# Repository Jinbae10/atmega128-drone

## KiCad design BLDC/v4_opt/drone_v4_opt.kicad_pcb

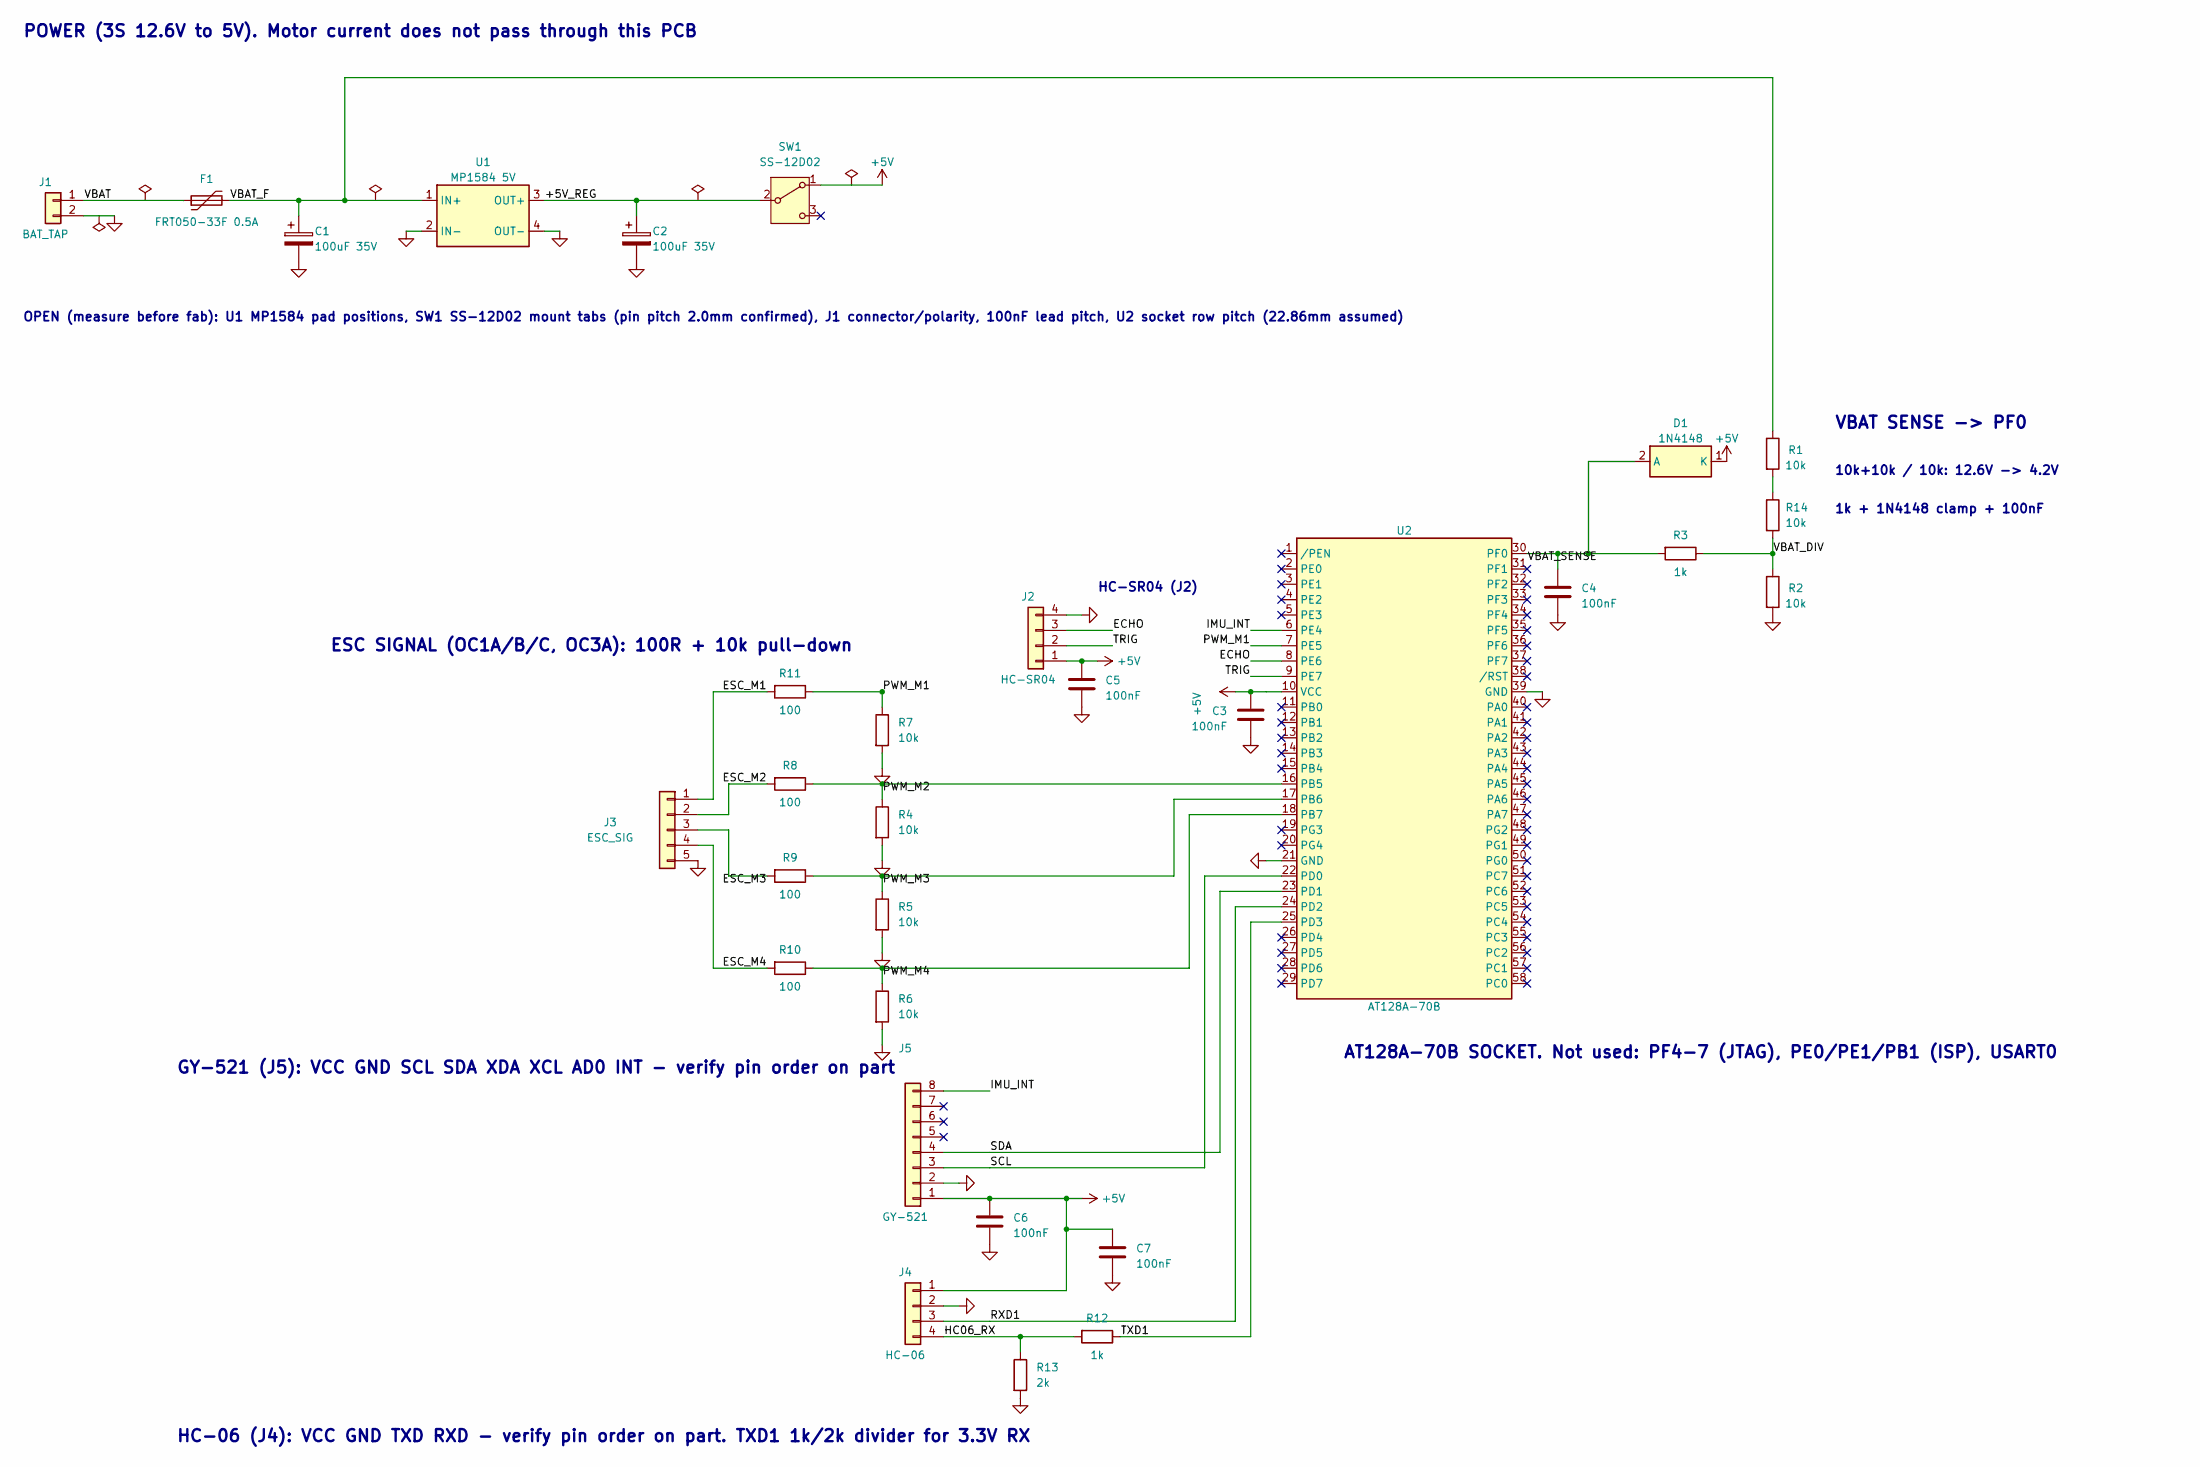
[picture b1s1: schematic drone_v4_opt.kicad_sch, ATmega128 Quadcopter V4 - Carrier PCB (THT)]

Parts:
C1, C2: 100uF 35V; CP_Radial_D6.3mm_P2.50mm
C3, C4, C5, C6, C7: 100nF; C_Disc_D4.3mm_W1.9mm_P5.00mm
D1: 1N4148; D_DO-35_SOD27_P7.62mm_Horizontal
F1: FRT050-33F 0.5A; Fuse_FRT050-33F_P5.10; MPN FRT050-33F
J1: BAT_TAP; PinHeader_1x02_P2.54mm_Vertical
J2: HC-SR04; PinSocket_1x04_P2.54mm_Vertical
J3: ESC_SIG; PinHeader_1x05_P2.54mm_Vertical
J4: HC-06; PinSocket_1x04_P2.54mm_Vertical
J5: GY-521; PinSocket_1x08_P2.54mm_Vertical
R1, R2, R4, R5, R6, R7, R14: 10k; R_Axial_DIN0204_L3.6mm_D1.6mm_P7.62mm_Horizontal
R3, R12: 1k; R_Axial_DIN0204_L3.6mm_D1.6mm_P7.62mm_Horizontal
R8, R9, R10, R11: 100; R_Axial_DIN0204_L3.6mm_D1.6mm_P7.62mm_Horizontal
R13: 2k; R_Axial_DIN0204_L3.6mm_D1.6mm_P7.62mm_Horizontal
SW1: SS-12D02; SW_SS-12D02_P2.00
U1: MP1584 5V; MP1584_Module_22x17
U2: AT128A-70B; AT128A-70B_Socket

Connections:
+5V: C3.1, C5.1, C6.1, C7.1, D1.1 (K), J2.1, J4.1, J5.1, SW1.1 (A), U2.10 (VCC)
/+5V_REG: C2.1, SW1.2 (B), U1.3 (OUT+)
/ECHO: J2.3, U2.8 (PE6)
/ESC_M1: J3.1, R11.2
/ESC_M2: J3.2, R8.2
/ESC_M3: J3.3, R9.2
/ESC_M4: J3.4, R10.2
/HC06_RX: J4.4, R12.2, R13.1
/IMU_INT: J5.8, U2.6 (PE4)
/PWM_M1: R7.1, R11.1, U2.7 (PE5)
/PWM_M2: R4.1, R8.1, U2.16 (PB5)
/PWM_M3: R5.1, R9.1, U2.17 (PB6)
/PWM_M4: R6.1, R10.1, U2.18 (PB7)
/RXD1: J4.3, U2.24 (PD2)
/SCL: J5.3, U2.22 (PD0)
/SDA: J5.4, U2.23 (PD1)
/TRIG: J2.2, U2.9 (PE7)
/TXD1: R12.1, U2.25 (PD3)
/VBAT: F1.1, J1.1
/VBAT_DIV: R2.1, R3.1, R14.2
/VBAT_F: C1.1, F1.2, R1.1, U1.1 (IN+)
/VBAT_SENSE: C4.1, D1.2 (A), R3.2, U2.30 (PF0)
GND: C1.2, C2.2, C3.2, C4.2, C5.2, C6.2, C7.2, J1.2, J2.4, J3.5, J4.2, J5.2, R2.2, R4.2, R5.2, R6.2, R7.2, R13.2, U1.2 (IN-), U1.4 (OUT-), U2.21 (GND), U2.39 (GND)
unnamed: R1.2, R14.1

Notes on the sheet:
POWER (3S 12.6V to 5V). Motor current does not pass through this PCB
OPEN (measure before fab): U1 MP1584 pad positions, SW1 SS-12D02 mount tabs (pin pitch 2.0mm confirmed), J1 connector/polarity, 100nF lead pitch, U2 socket row pitch (22.86mm assumed)
VBAT SENSE -> PF0
10k+10k / 10k: 12.6V -> 4.2V
1k + 1N4148 clamp + 100nF
AT128A-70B SOCKET. Not used: PF4-7 (JTAG), PE0/PE1/PB1 (ISP), USART0
HC-SR04 (J2)
ESC SIGNAL (OC1A/B/C, OC3A): 100R + 10k pull-down
GY-521 (J5): VCC GND SCL SDA XDA XCL AD0 INT - verify pin order on part
HC-06 (J4): VCC GND TXD RXD - verify pin order on part. TXD1 1k/2k divider for 3.3V RX

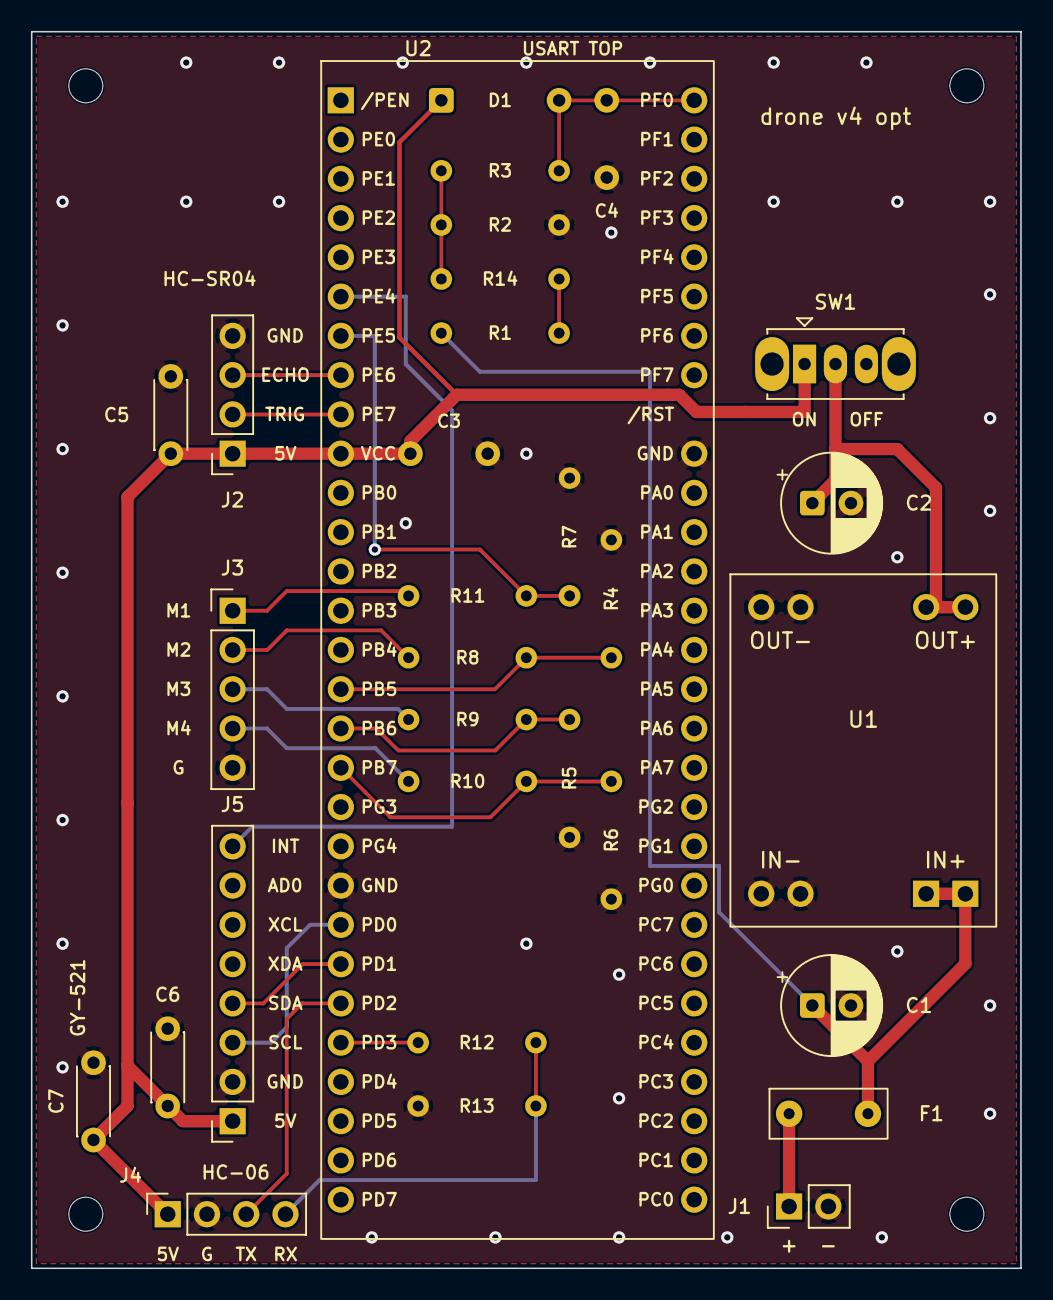
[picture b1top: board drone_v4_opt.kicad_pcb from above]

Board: 2 copper layers, 64.0 x 80.0 mm, 35 parts (0 on the bottom side), 24 nets.

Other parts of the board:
MH1, MH2, MH3, MH4: MountingHole_2.2mm

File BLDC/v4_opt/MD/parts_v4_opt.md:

# 부품 목록 (v4_opt, 최종)

- 기준일: 2026-11-18. 값·수량은 [drone_v4_opt.kicad_sch](../drone_v4_opt.kicad_sch) BOM 기준(v4와 소자·수량 동일, 배치·MCU 핀만 다름).
- 가격은 **VAT 포함**, 디바이스마트 상품 페이지 값(2026-11-17~18 확인). 상세 근거는 [../../v4/MD/parts_v4.md](../../v4/MD/parts_v4.md).
- **v4_opt 주의**: 모듈(U2) 아래에 저항 14개·D1·C3·C4가 들어가므로 U2 암헤더는 반드시 **8.5mm 높이(VLT-PH054 Type 1)**. 저항·D1·C3·C4를 먼저 납땜한 뒤 암헤더를 납땜합니다.

## 1. 납땜 소자 (디바이스마트)

| 회로도 번호 | 소자 | 상품 | 필요 | 구매 단위 | 가격 |
|---|---|---|---|---|---|
| R1, R2, R4~R7, R14 | 10k 1/8W 1% (20k = R1+R14 직렬) | [no=1907](https://www.devicemart.co.kr/goods/view?no=1907) | 7 | 10개 | 330원 |
| R3, R12 | 1k 1/8W | [no=2150](https://www.devicemart.co.kr/goods/view?no=2150) | 2 | 10개 | 165원 |
| R13 | 2k 1/8W | [no=2146](https://www.devicemart.co.kr/goods/view?no=2146) | 1 | 10개 | 165원 |
| R8~R11 | 100Ω 1/8W | [no=2166](https://www.devicemart.co.kr/goods/view?no=2166) | 4 | 10개 | 165원 |
| C3~C7 | 100nF 50V 적층 세라믹 | [no=1399](https://www.devicemart.co.kr/goods/view?no=1399) | 5 | 10개 | 330원 |
| F1 | 폴리퓨즈 FRT050-33F 0.5A 33V | [no=10918593](https://www.devicemart.co.kr/goods/view?no=10918593) | 1 | 10개 | 1,540원 |
| D1 | 1N4148 DO-35 | [no=25](https://www.devicemart.co.kr/goods/view?no=25) | 1 | 10개 | 220원 |
| C1, C2 | 전해 100µF 35V Ø6.3×11 | [no=12211007](https://www.devicemart.co.kr/goods/view?no=12211007) | 2 | 10개 | 440원 |
| SW1 | 슬라이드 SS-12D02 | [no=14572](https://www.devicemart.co.kr/goods/view?no=14572) | 1 | 1개 | 165원 |
| J1, J3, U1 장착 | 수 핀헤더 1×40 2.54mm | [no=2825](https://www.devicemart.co.kr/goods/view?no=2825) | 1줄 | 1줄 | 220원 |
| | | | | **소계** | **약 3,740원** |

## 2. 모듈 (디바이스마트)

| 부품 | 상품 | 수량 | 가격 |
|---|---|---|---|
| MPU-6050 GY-521 | [no=1247052](https://www.devicemart.co.kr/goods/view?no=1247052) | 1 | 4,950원 |
| HC-06 DIP 슬레이브 | [no=1376882](https://www.devicemart.co.kr/goods/view?no=1376882) | 1 | 6,050원 |
| MP1584 강압 모듈 SZH-PWSD-002 | [no=1321132](https://www.devicemart.co.kr/goods/view?no=1321132) | 1 | 2,200원 |
| | | **소계** | **13,200원** |

## 3. PCB 밖 (디바이스마트)

| 부품 | 상품 | 수량 | 가격 |
|---|---|---|---|
| 암 핀헤더 1×40 **8.5mm** (VLT-PH054) — U2·센서 소켓 | [no=15959307](https://www.devicemart.co.kr/goods/view?no=15959307) | 3 (2개면 74핀 충분, 1개 예비) | 1,320원 |
| XT60 암수 세트 | [no=1078005](https://www.devicemart.co.kr/goods/view?no=1078005) | 2 | 3,520원 |
| 열수축 튜브 5파이 1m | [no=1065347](https://www.devicemart.co.kr/goods/view?no=1065347) | 1 | 253원 |
| 프로펠러 SMG 5030 2엽 CW/CCW | [no=1342513](https://www.devicemart.co.kr/goods/view?no=1342513) | 3쌍 | 8,580원 |

## 4. 합계 (VAT 포함)

| 구분 | 금액 |
|---|---|
| 납땜 소자 | 약 3,740원 |
| 모듈 | 13,200원 |
| PCB 밖 (암헤더·XT60·열수축·프로펠러) | 13,673원 |
| **디바이스마트 부품 합계** | **약 30,613원** |
| PCB 제작 (사용자 확인 가격, 64×80mm 조건 미확인) | 19,000원 |
| 배송비 | 2,700원 |
| **디바이스마트 총액** | **약 52,313원** |

- 2026-11-18 장바구니(PCB 제외): 33,313원(배송 포함).
- `parts_v4.md` 합계(29,293원)에는 암헤더 1,320원이 빠져 있어 여기서는 포함했습니다.
- 이미 구매: 모터 MT2204 2300KV ×4, ESC LittleBee-Spring 20A ×4, 3S LiPo 1300mAh 90C XT60, 충전기 Imax B3 Pro. 보유·대여: HC-SR04, ATmega128A 모듈, JTAG ICE, AR-UART2USB.

## 5. 주문 전 확인

1. 100nF 리드 간격, SS-12D02 고정 탭, MP1584 모듈 패드 위치 (실측)
2. SW1 ON 방향(실크 ON/OFF는 추정) — 멀티미터 확인
3. 암헤더 높이 8.5mm 제품인지 확인

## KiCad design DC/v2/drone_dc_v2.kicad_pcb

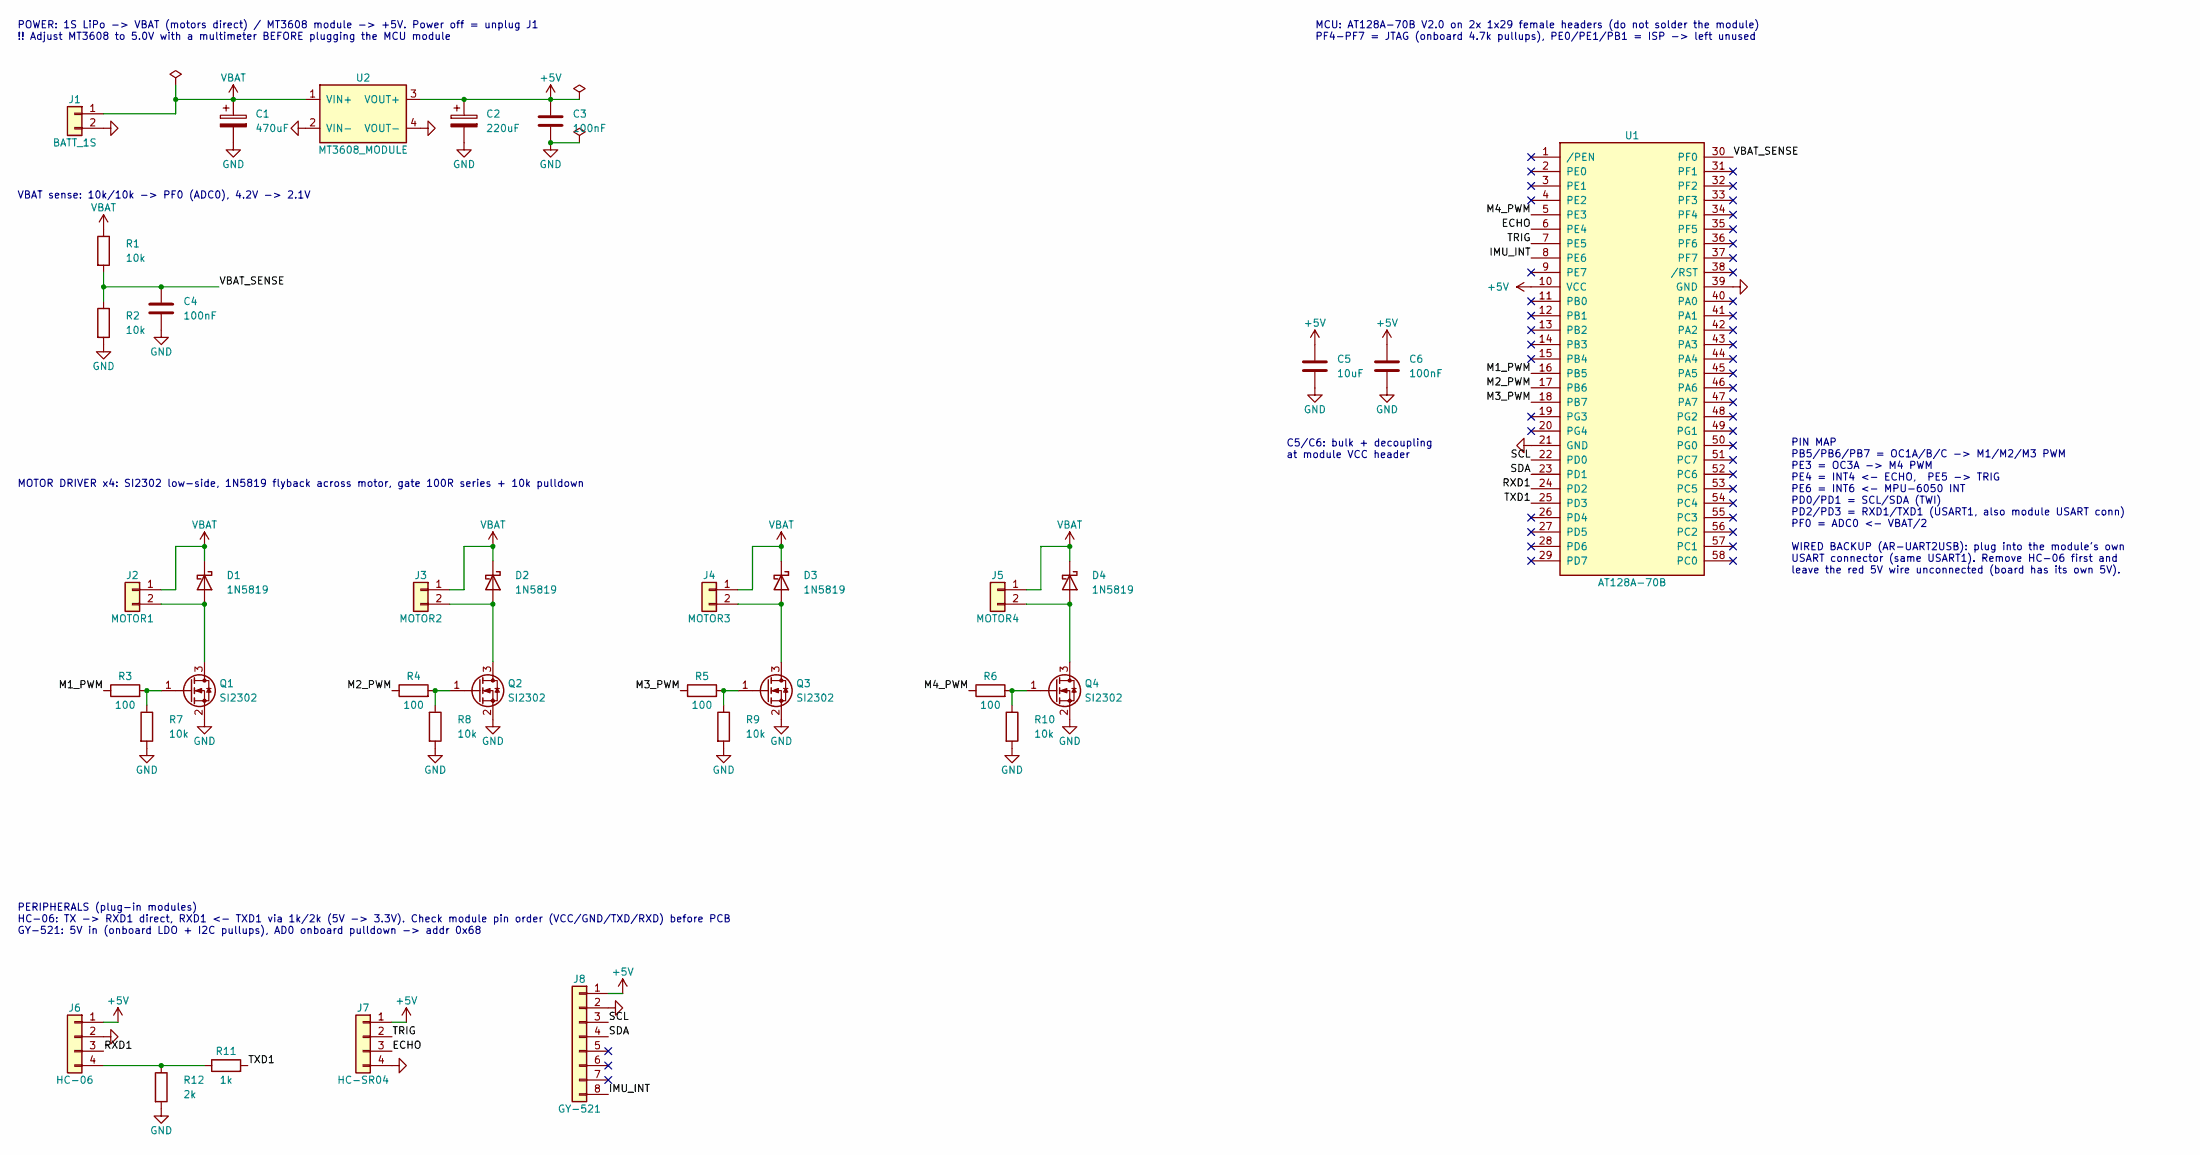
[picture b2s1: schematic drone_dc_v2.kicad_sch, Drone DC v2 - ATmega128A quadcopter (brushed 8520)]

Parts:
C1: 470uF; CP_Radial_D8.0mm_P3.50mm
C2: 220uF; CP_Radial_D6.3mm_P2.50mm
C3, C4, C6: 100nF; C_Disc_D3.0mm_W1.6mm_P2.50mm
C5: 10uF; CP_Radial_D5.0mm_P2.00mm
D1, D2, D3, D4: 1N5819; D_DO-41_SOD81_P5.08mm_Vertical_AnodeUp
J1: BATT_1S; JST_PH_B2B-PH-K_1x02_P2.00mm_Vertical
J2: MOTOR1; PinHeader_1x02_P2.54mm_Vertical
J3: MOTOR2; PinHeader_1x02_P2.54mm_Vertical
J4: MOTOR3; PinHeader_1x02_P2.54mm_Vertical
J5: MOTOR4; PinHeader_1x02_P2.54mm_Vertical
J6: HC-06; PinSocket_1x04_P2.54mm_Vertical
J7: HC-SR04; PinSocket_1x04_P2.54mm_Vertical
J8: GY-521; PinSocket_1x08_P2.54mm_Vertical
Q1, Q2, Q3, Q4: SI2302; SOT-23_Handsoldering
R1, R2, R7, R8, R9, R10: 10k; R_Axial_DIN0207_L6.3mm_D2.5mm_P2.54mm_Vertical
R3, R4, R5, R6: 100; R_Axial_DIN0207_L6.3mm_D2.5mm_P2.54mm_Vertical
R11: 1k; R_Axial_DIN0207_L6.3mm_D2.5mm_P2.54mm_Vertical
R12: 2k; R_Axial_DIN0207_L6.3mm_D2.5mm_P2.54mm_Vertical
U1: AT128A-70B; AT128A-70B_Module
U2: MT3608_MODULE; MT3608_Module_Wire

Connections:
+5V: C2.1, C3.1, C5.1, C6.1, J6.1, J7.1, J8.1, U1.10 (VCC), U2.3 (VOUT+)
/ECHO: J7.3, U1.6 (PE4)
/IMU_INT: J8.8, U1.8 (PE6)
/M1_PWM: R3.1, U1.16 (PB5)
/M2_PWM: R4.1, U1.17 (PB6)
/M3_PWM: R5.1, U1.18 (PB7)
/M4_PWM: R6.1, U1.5 (PE3)
/RXD1: J6.3, U1.24 (PD2)
/SCL: J8.3, U1.22 (PD0)
/SDA: J8.4, U1.23 (PD1)
/TRIG: J7.2, U1.7 (PE5)
/TXD1: R11.2, U1.25 (PD3)
/VBAT_SENSE: C4.1, R1.2, R2.1, U1.30 (PF0)
GND: C1.2, C2.2, C3.2, C4.2, C5.2, C6.2, J1.2, J6.2, J7.4, J8.2, Q1.2 (S), Q2.2 (S), Q3.2 (S), Q4.2 (S), R2.2, R7.2, R8.2, R9.2, R10.2, R12.2, U1.21 (GND), U1.39 (GND), U2.2 (VIN-), U2.4 (VOUT-)
unnamed: D1.2 (A), J2.2, Q1.3 (D)
unnamed: D2.2 (A), J3.2, Q2.3 (D)
unnamed: D3.2 (A), J4.2, Q3.3 (D)
unnamed: D4.2 (A), J5.2, Q4.3 (D)
unnamed: J6.4, R11.1, R12.1
unnamed: Q1.1 (G), R3.2, R7.1
unnamed: Q2.1 (G), R4.2, R8.1
unnamed: Q3.1 (G), R5.2, R9.1
unnamed: Q4.1 (G), R6.2, R10.1
VBAT: C1.1, D1.1 (K), D2.1 (K), D3.1 (K), D4.1 (K), J1.1, J2.1, J3.1, J4.1, J5.1, R1.1, U2.1 (VIN+)

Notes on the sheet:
POWER: 1S LiPo -> VBAT (motors direct) / MT3608 module -> +5V. Power off = unplug J1 !! Adjust MT3608 to 5.0V with a multimeter BEFORE plugging the MCU module
VBAT sense: 10k/10k -> PF0 (ADC0), 4.2V -> 2.1V
MOTOR DRIVER x4: SI2302 low-side, 1N5819 flyback across motor, gate 100R series + 10k pulldown
PERIPHERALS (plug-in modules) HC-06: TX -> RXD1 direct, RXD1 <- TXD1 via 1k/2k (5V -> 3.3V). Check module pin order (VCC/GND/TXD/RXD) before PCB GY-521: 5V in (onboard LDO + I2C pullups), AD0 onboard pulldown -> addr 0x68
MCU: AT128A-70B V2.0 on 2x 1x29 female headers (do not solder the module) PF4-PF7 = JTAG (onboard 4.7k pullups), PE0/PE1/PB1 = ISP -> left unused
C5/C6: bulk + decoupling at module VCC header
PIN MAP PB5/PB6/PB7 = OC1A/B/C -> M1/M2/M3 PWM PE3 = OC3A -> M4 PWM PE4 = INT4 <- ECHO, PE5 -> TRIG PE6 = INT6 <- MPU-6050 INT PD0/PD1 = SCL/SDA (TWI) PD2/PD3 = RXD1/TXD1 (USART1, also module USART conn) PF0 = ADC0 <- VBAT/2 WIRED BACKUP (AR-UART2USB): plug into the module's own USART connector (sa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

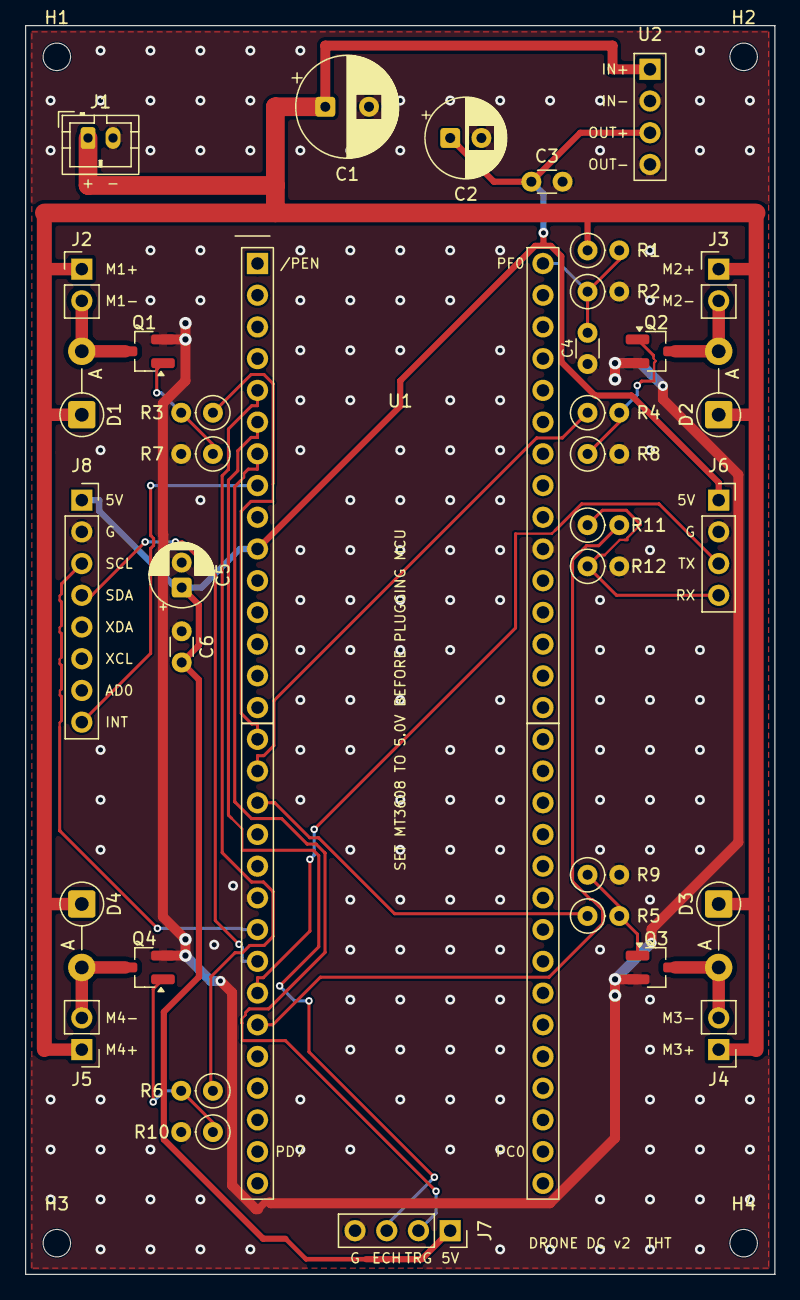
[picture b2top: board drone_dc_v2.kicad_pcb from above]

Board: 2 copper layers, 60.0 x 100.0 mm, 40 parts (0 on the bottom side), 24 nets.

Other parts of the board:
H1, H2, H3, H4: M2; MountingHole_2.2mm_M2

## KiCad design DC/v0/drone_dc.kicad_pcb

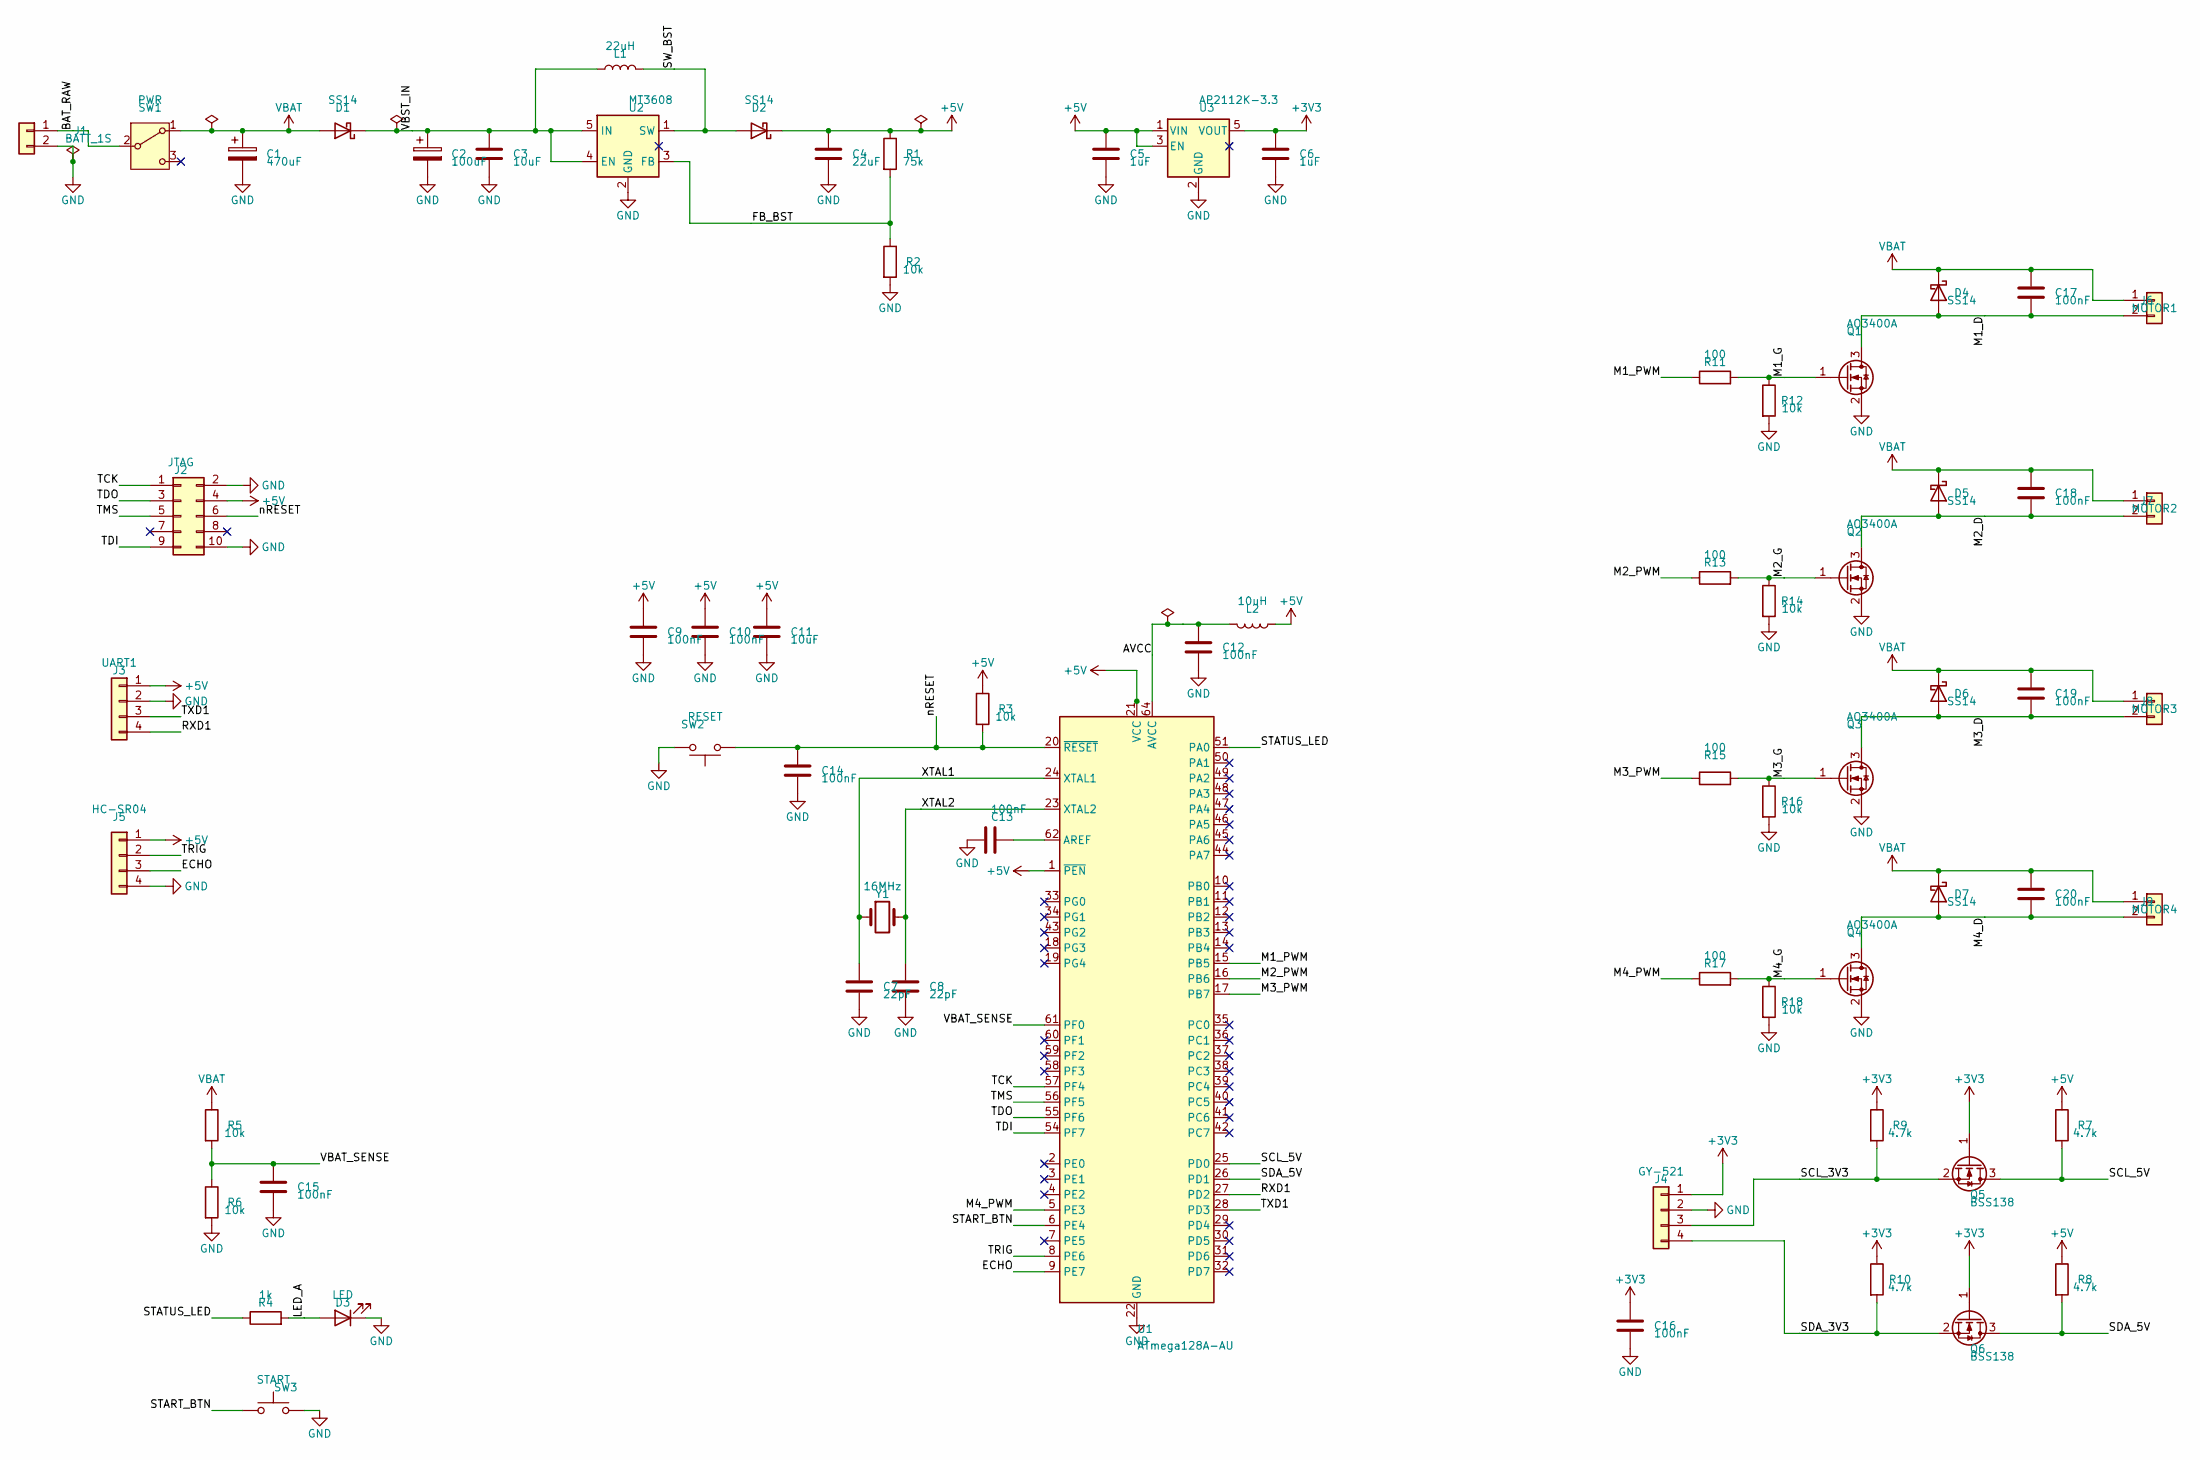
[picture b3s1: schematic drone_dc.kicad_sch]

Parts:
C1: 470uF; CP_Elec_8x10
C2: 100uF; CP_Elec_6.3x7.7
C3, C11: 10uF; C_0805_2012Metric
C4: 22uF; C_0805_2012Metric
C5, C6: 1uF; C_0603_1608Metric
C7, C8: 22pF; C_0603_1608Metric
C9, C10, C12, C13, C14, C15, C16, C17, C18, C19, C20: 100nF; C_0603_1608Metric
D1, D2, D4, D5, D6, D7: SS14; D_SMA
D3: LED; LED_0603_1608Metric
J1: BATT_1S; JST_PH_B2B-PH-K_1x02_P2.00mm_Vertical
J2: JTAG; PinHeader_2x05_P2.54mm_Vertical
J3: UART1; PinHeader_1x04_P2.54mm_Vertical
J4: GY-521; PinHeader_1x04_P2.54mm_Vertical
J5: HC-SR04; PinHeader_1x04_P2.54mm_Vertical
J6: MOTOR1; JST_PH_B2B-PH-K_1x02_P2.00mm_Vertical
J7: MOTOR2; JST_PH_B2B-PH-K_1x02_P2.00mm_Vertical
J8: MOTOR3; JST_PH_B2B-PH-K_1x02_P2.00mm_Vertical
J9: MOTOR4; JST_PH_B2B-PH-K_1x02_P2.00mm_Vertical
L1: 22uH; L_Bourns_SRN6045TA
L2: 10uH; L_0805_2012Metric
Q1, Q2, Q3, Q4: AO3400A; SOT-23
Q5, Q6: BSS138; SOT-23
R1: 75k; R_0603_1608Metric
R2, R3, R5, R6, R12, R14, R16, R18: 10k; R_0603_1608Metric
R4: 1k; R_0603_1608Metric
R7, R8, R9, R10: 4.7k; R_0603_1608Metric
R11, R13, R15, R17: 100; R_0603_1608Metric
SW1: PWR; SW_SPDT_PCM12
SW2: RESET; SW_SPST_TL3342
SW3: START; SW_SPST_TL3342
U1: ATmega128A-AU; TQFP-64_14x14mm_P0.8mm
U2: MT3608; SOT-23-6
U3: AP2112K-3.3; SOT-23-5
Y1: 16MHz; Crystal_SMD_HC49-SD

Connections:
+3V3: C6.1, C16.1, J4.1, Q5.1 (G), Q6.1 (G), R9.1, R10.1, U3.5 (VOUT)
+5V: C4.1, C5.1, C9.1, C10.1, C11.1, D2.1 (K), J2.4, J3.1, J5.1, L2.1, R1.1, R3.1, R7.1, R8.1, U1.1 (~PEN), U1.21 (VCC), U1.52 (VCC), U3.1 (VIN), U3.3 (EN)
AVCC: C12.1, L2.2, U1.64 (AVCC)
BAT_RAW: J1.1, SW1.2 (B)
ECHO: J5.3, U1.9 (PE7)
FB_BST: R1.2, R2.1, U2.3 (FB)
GND: C1.2, C2.2, C3.2, C4.2, C5.2, C6.2, C7.2, C8.2, C9.2, C10.2, C11.2, C12.2, C13.2, C14.2, C15.2, C16.2, D3.1 (K), J1.2, J2.2, J2.10, J3.2, J4.2, J5.4, Q1.2 (S), Q2.2 (S), Q3.2 (S), Q4.2 (S), R2.2, R6.2, R12.2, R14.2, R16.2, R18.2, SW2.2, SW3.2, U1.22 (GND), U1.53 (GND), U1.63 (GND), U2.2 (GND), U3.2 (GND)
LED_A: D3.2 (A), R4.2
M1_D: C17.2, D4.2 (A), J6.2, Q1.3 (D)
M1_G: Q1.1 (G), R11.2, R12.1
M1_PWM: R11.1, U1.15 (PB5)
M2_D: C18.2, D5.2 (A), J7.2, Q2.3 (D)
M2_G: Q2.1 (G), R13.2, R14.1
M2_PWM: R13.1, U1.16 (PB6)
M3_D: C19.2, D6.2 (A), J8.2, Q3.3 (D)
M3_G: Q3.1 (G), R15.2, R16.1
M3_PWM: R15.1, U1.17 (PB7)
M4_D: C20.2, D7.2 (A), J9.2, Q4.3 (D)
M4_G: Q4.1 (G), R17.2, R18.1
M4_PWM: R17.1, U1.5 (PE3)
unnamed: C13.1, U1.62 (AREF)
RXD1: J3.4, U1.27 (PD2)
SCL_3V3: J4.3, Q5.2 (S), R9.2
SCL_5V: Q5.3 (D), R7.2, U1.25 (PD0)
SDA_3V3: J4.4, Q6.2 (S), R10.2
SDA_5V: Q6.3 (D), R8.2, U1.26 (PD1)
START_BTN: SW3.1, U1.6 (PE4)
STATUS_LED: R4.1, U1.51 (PA0)
SW_BST: D2.2 (A), L1.2, U2.1 (SW)
TCK: J2.1, U1.57 (PF4)
TDI: J2.9, U1.54 (PF7)
TDO: J2.3, U1.55 (PF6)
TMS: J2.5, U1.56 (PF5)
TRIG: J5.2, U1.8 (PE6)
TXD1: J3.3, U1.28 (PD3)
VBAT: C1.1, C17.1, C18.1, C19.1, C20.1, D1.2 (A), D4.1 (K), D5.1 (K), D6.1 (K), D7.1 (K), J6.1, J7.1, J8.1, J9.1, R5.1, SW1.1 (A)
VBAT_SENSE: C15.1, R5.2, R6.1, U1.61 (PF0)
VBST_IN: C2.1, C3.1, D1.1 (K), L1.1, U2.4 (EN), U2.5 (IN)
XTAL1: C7.1, U1.24 (XTAL1), Y1.1
XTAL2: C8.1, U1.23 (XTAL2), Y1.2
nRESET: C14.1, J2.6, R3.2, SW2.1, U1.20 (~RESET)

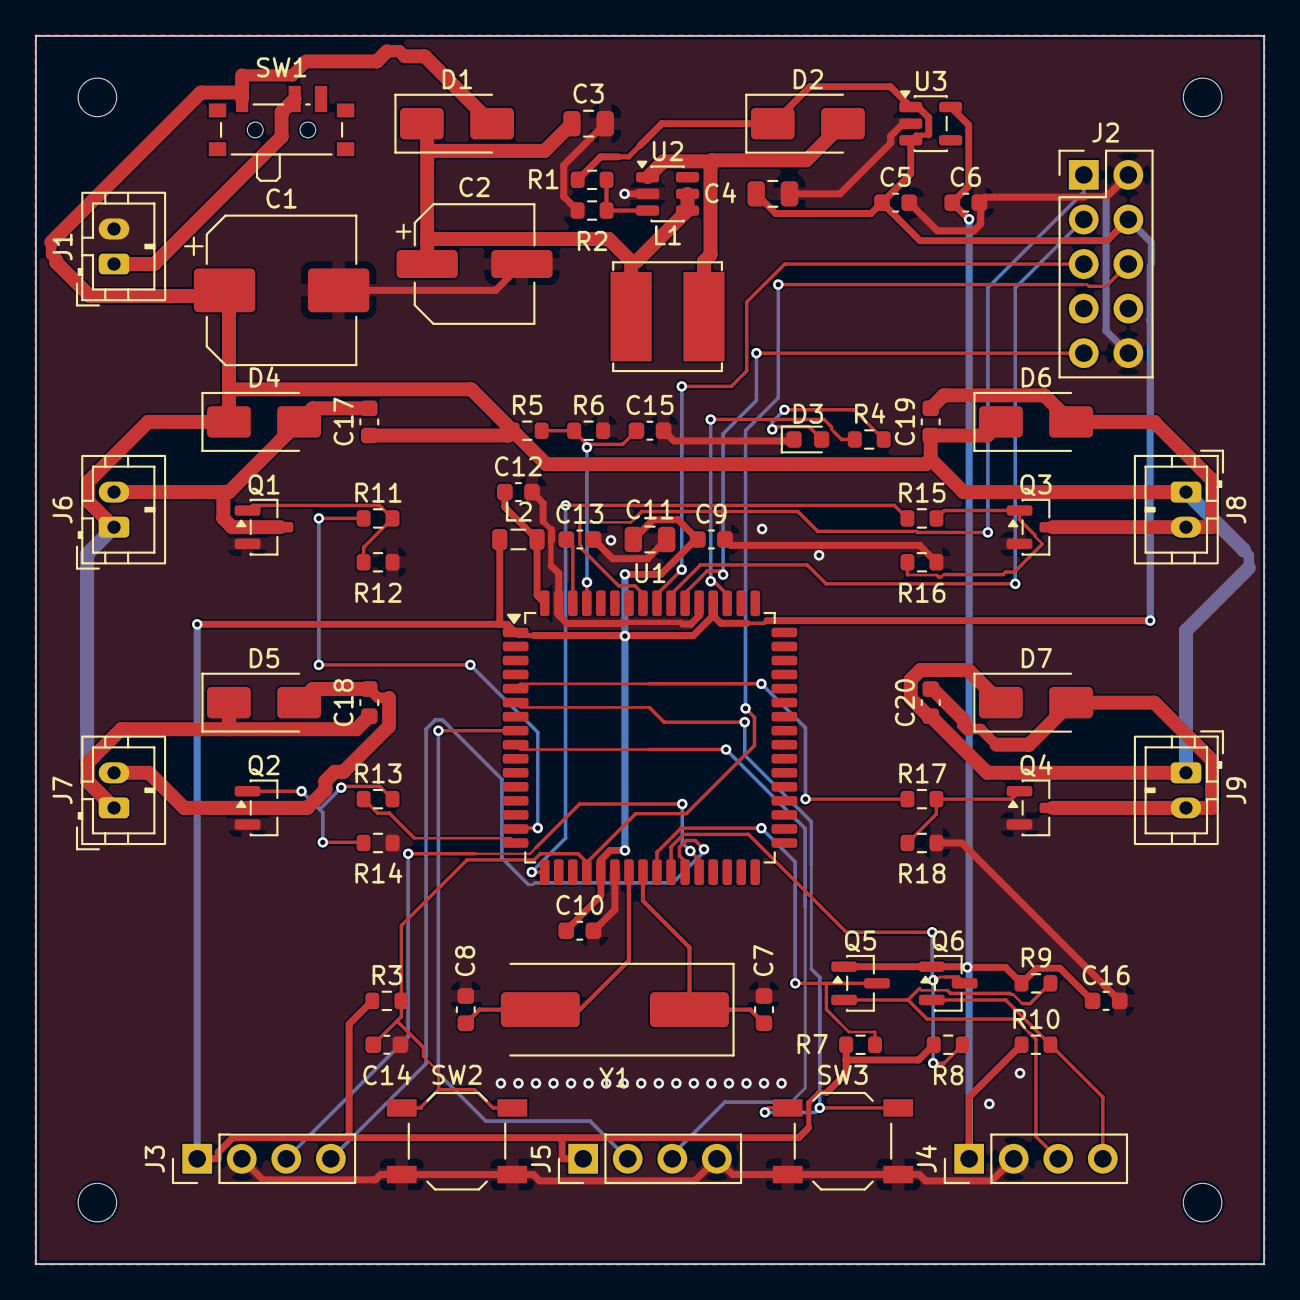
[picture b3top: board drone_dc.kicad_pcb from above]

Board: 2 copper layers, 70.0 x 70.0 mm, 73 parts (0 on the bottom side), 41 nets.

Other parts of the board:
H1, H2, H3, H4: MountingHole_2.2mm_M2
